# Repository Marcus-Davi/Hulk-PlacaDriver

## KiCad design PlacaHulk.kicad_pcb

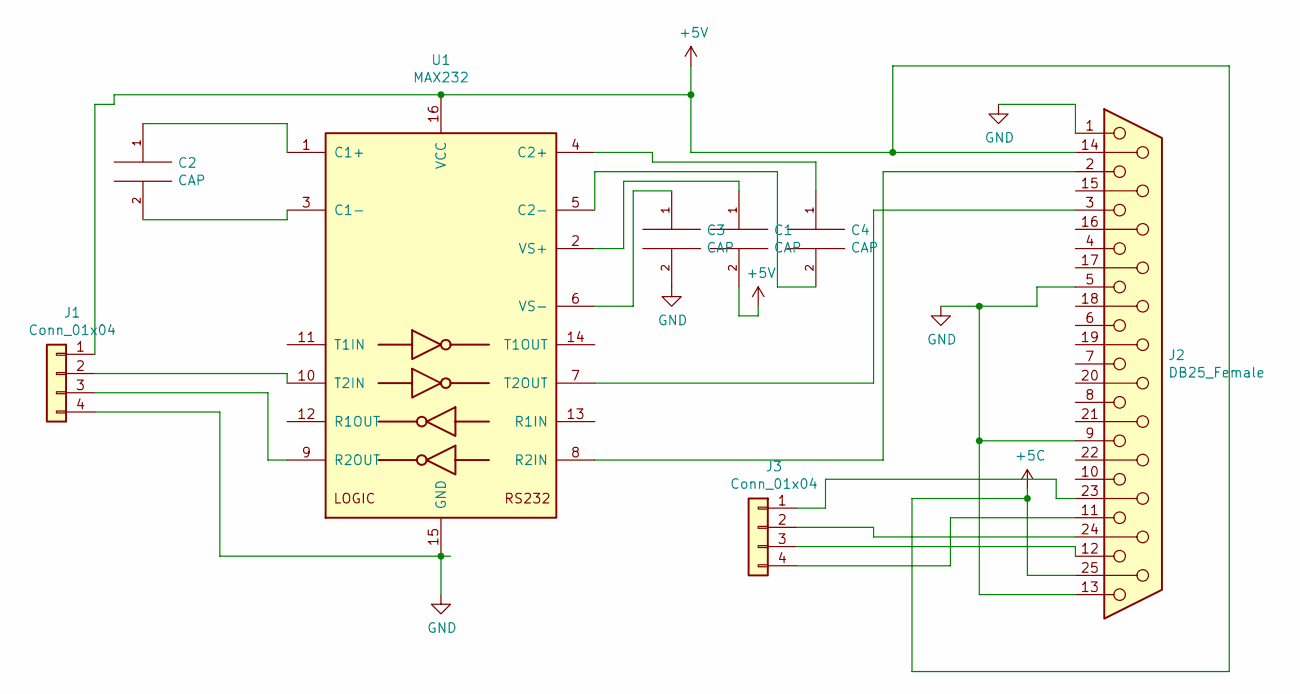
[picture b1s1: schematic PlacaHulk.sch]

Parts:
C1, C2, C3, C4: CAP; CP_Radial_D5.0mm_P2.50mm
J1, J3: Conn_01x04; PinSocket_1x04_P2.54mm_Vertical
J2: DB25_Female; DSUB-25_Female_Vertical_P2.77x2.84mm
U1: MAX232; DIP-16_W7.62mm

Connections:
+5C: C1.2, J1.1, J2.14, J2.25, U1.16 (VCC)
GND: C3.2, J1.4, J2.1, J2.5, J2.9, J2.13, U1.15 (GND)
unnamed: C1.1, U1.2 (VS+)
unnamed: C2.1, U1.1 (C1+)
unnamed: C2.2, U1.3 (C1-)
unnamed: C3.1, U1.6 (VS-)
unnamed: C4.1, U1.4 (C2+)
unnamed: C4.2, U1.5 (C2-)
unnamed: J1.2, U1.10 (T2IN)
unnamed: J1.3, U1.9 (R2OUT)
unnamed: J2.2, U1.8 (R2IN)
unnamed: J2.3, U1.7 (T2OUT)
unnamed: J2.11, J3.4
unnamed: J2.12, J3.3
unnamed: J2.23, J3.1
unnamed: J2.24, J3.2

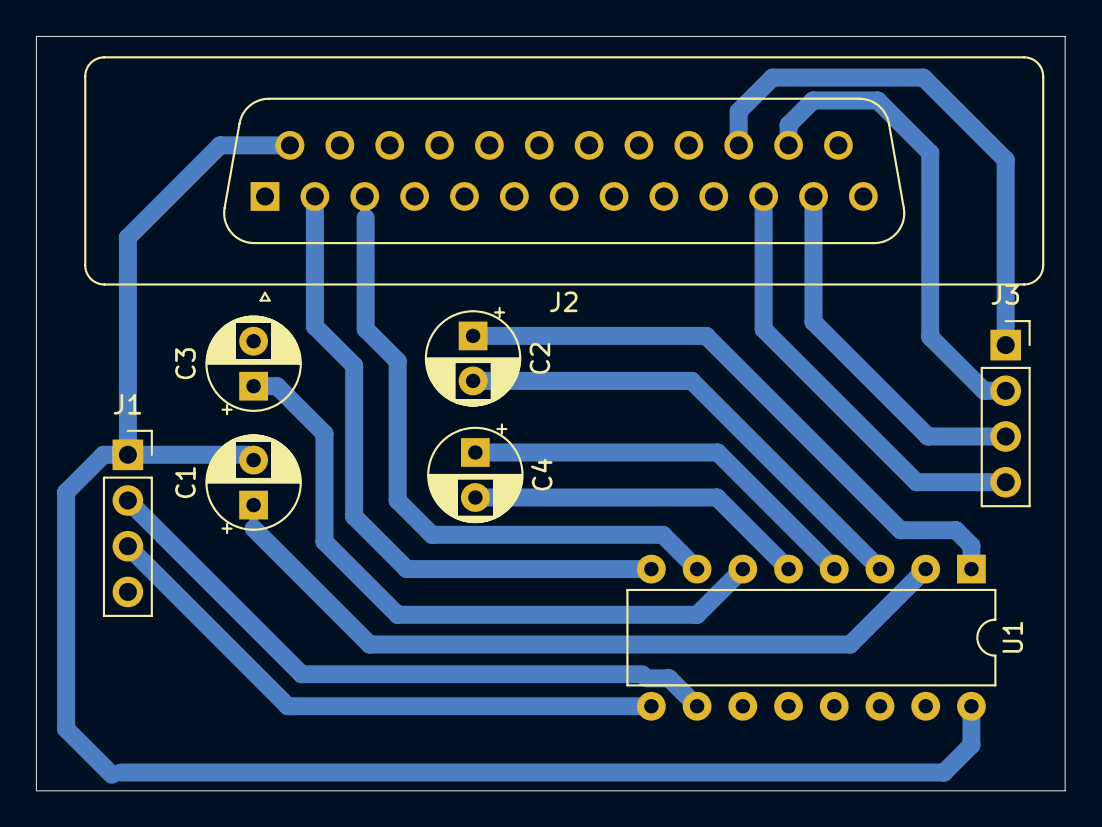
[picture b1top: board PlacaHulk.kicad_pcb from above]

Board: 2 copper layers, 57.2 x 41.9 mm, 8 parts (0 on the bottom side), 16 nets.

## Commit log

2020-02-13 first
2020-02-13 adicionei PCB
2020-02-14 Feito o layout da PCB.
2020-02-17 Mudado os pinos usados e o layout da PCB.
2020-02-20 Adicionado os conectores do encoder.
2020-02-20 Refeito o layout da Placa com os conectores do encoder.
2020-02-21 Aumentado a largura das trilhas.
2020-03-10 Adicionada foto de pinout.
